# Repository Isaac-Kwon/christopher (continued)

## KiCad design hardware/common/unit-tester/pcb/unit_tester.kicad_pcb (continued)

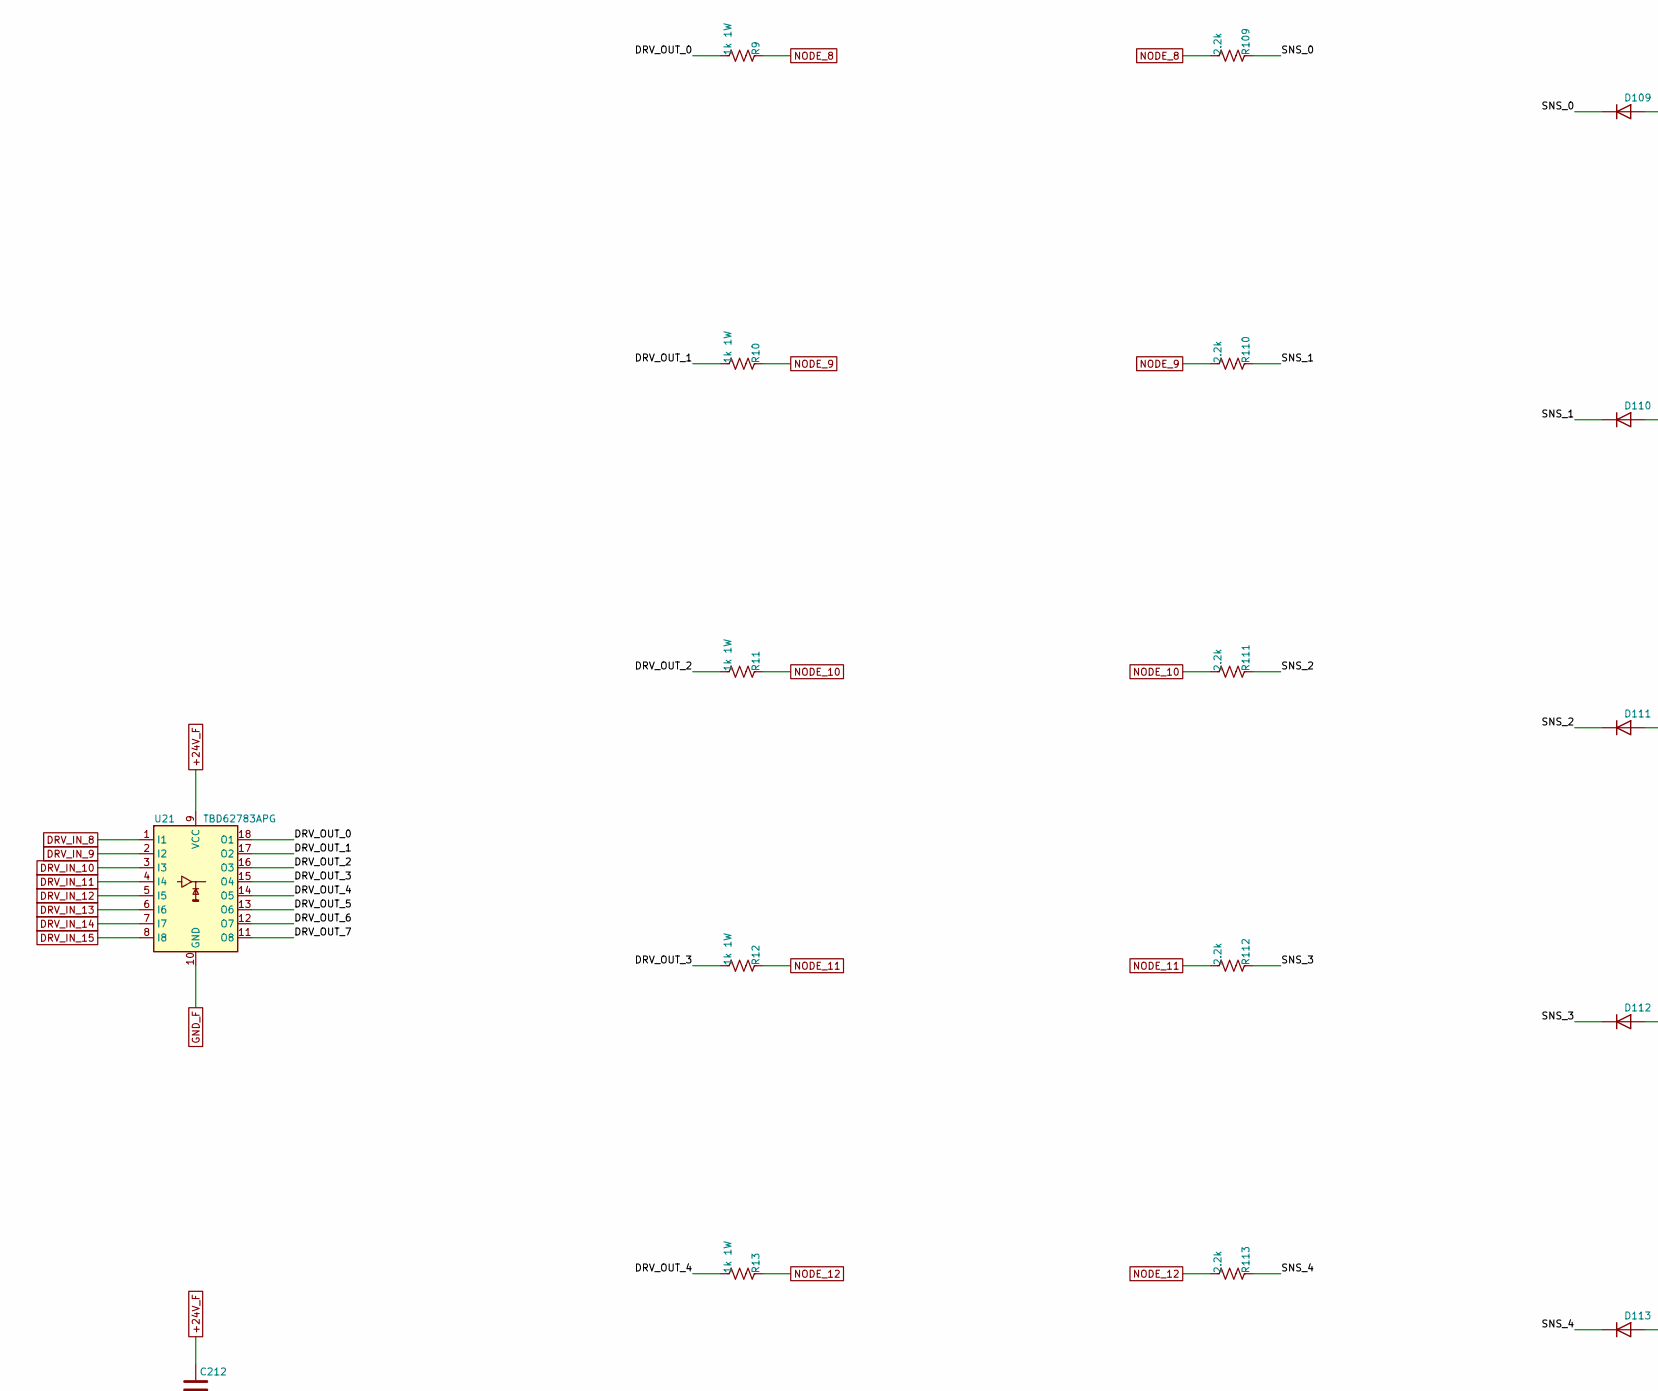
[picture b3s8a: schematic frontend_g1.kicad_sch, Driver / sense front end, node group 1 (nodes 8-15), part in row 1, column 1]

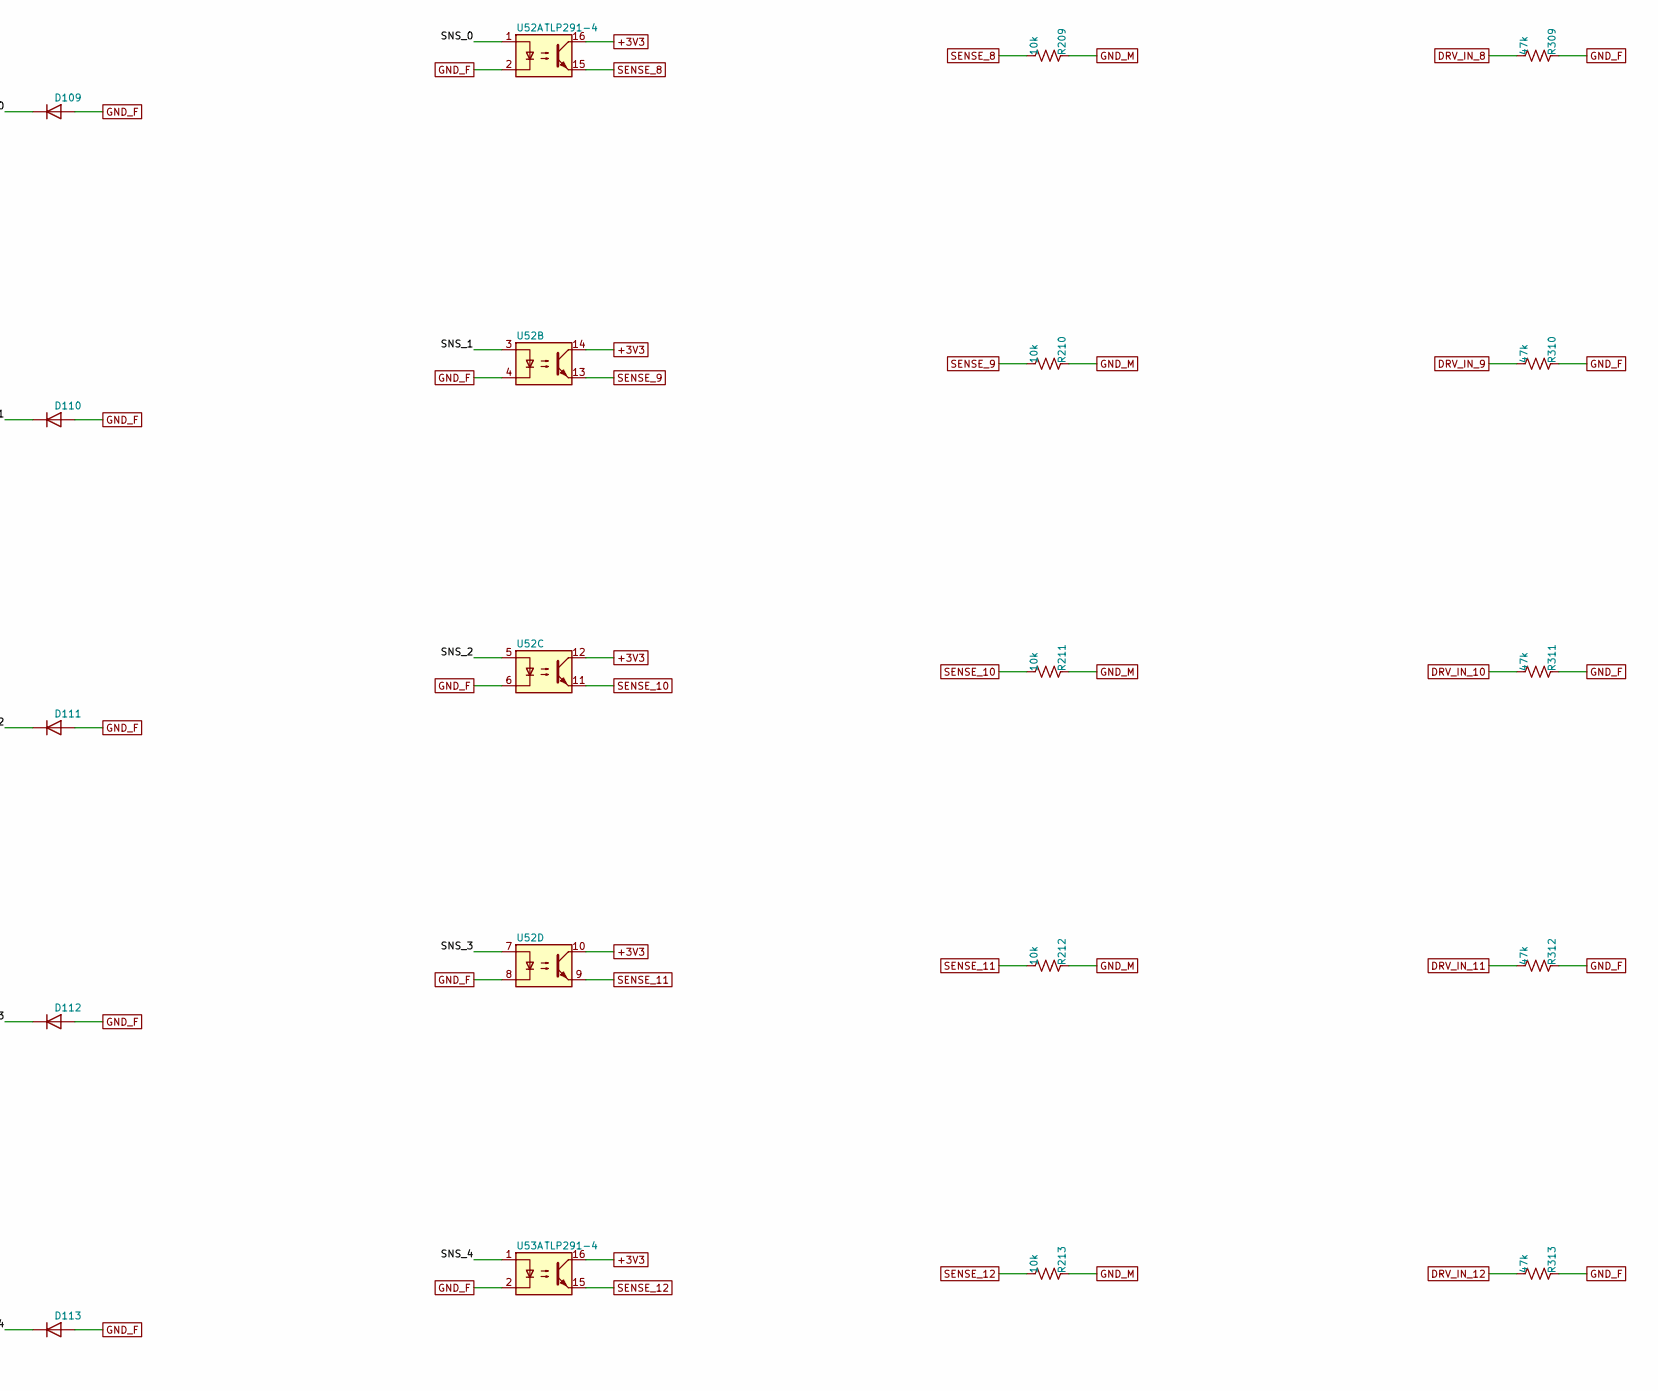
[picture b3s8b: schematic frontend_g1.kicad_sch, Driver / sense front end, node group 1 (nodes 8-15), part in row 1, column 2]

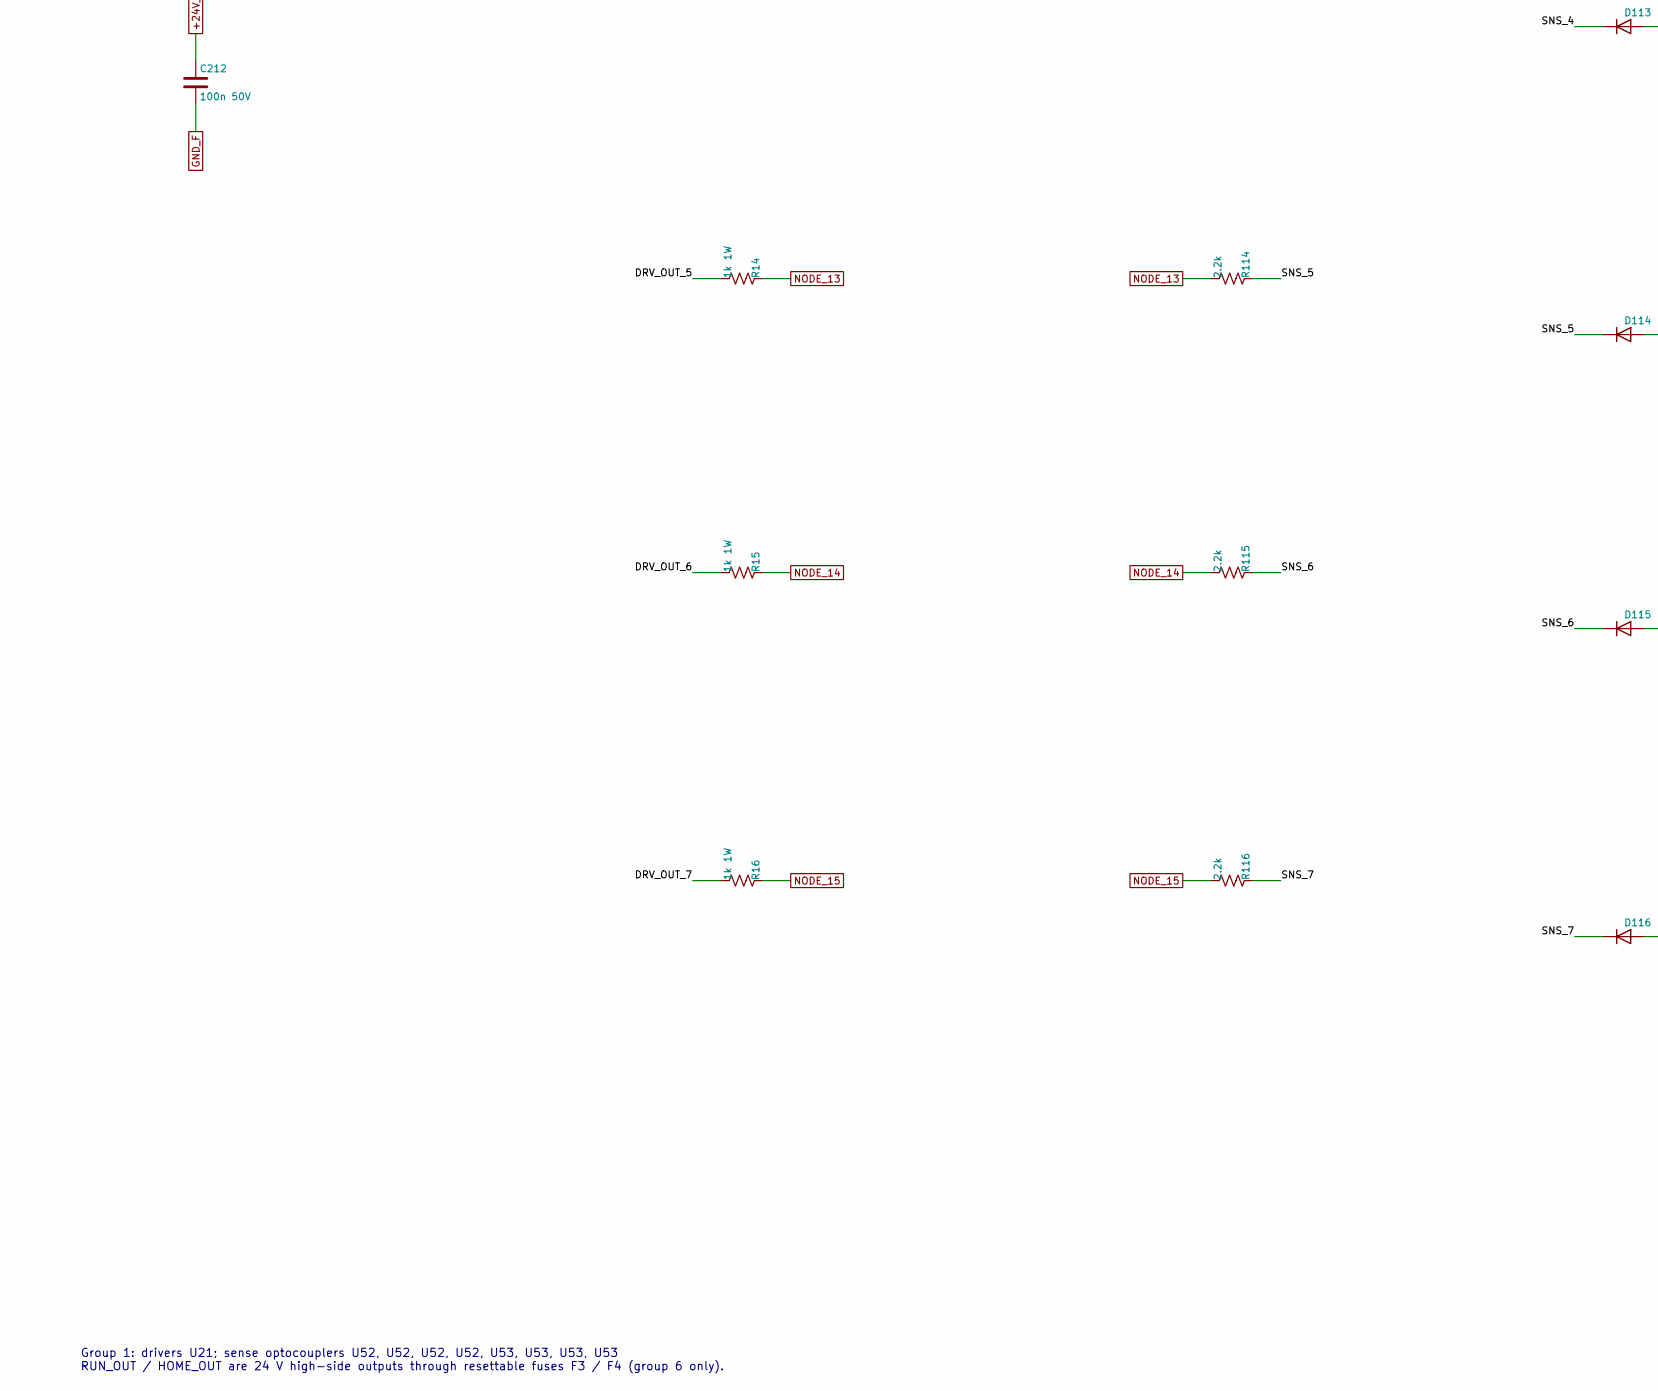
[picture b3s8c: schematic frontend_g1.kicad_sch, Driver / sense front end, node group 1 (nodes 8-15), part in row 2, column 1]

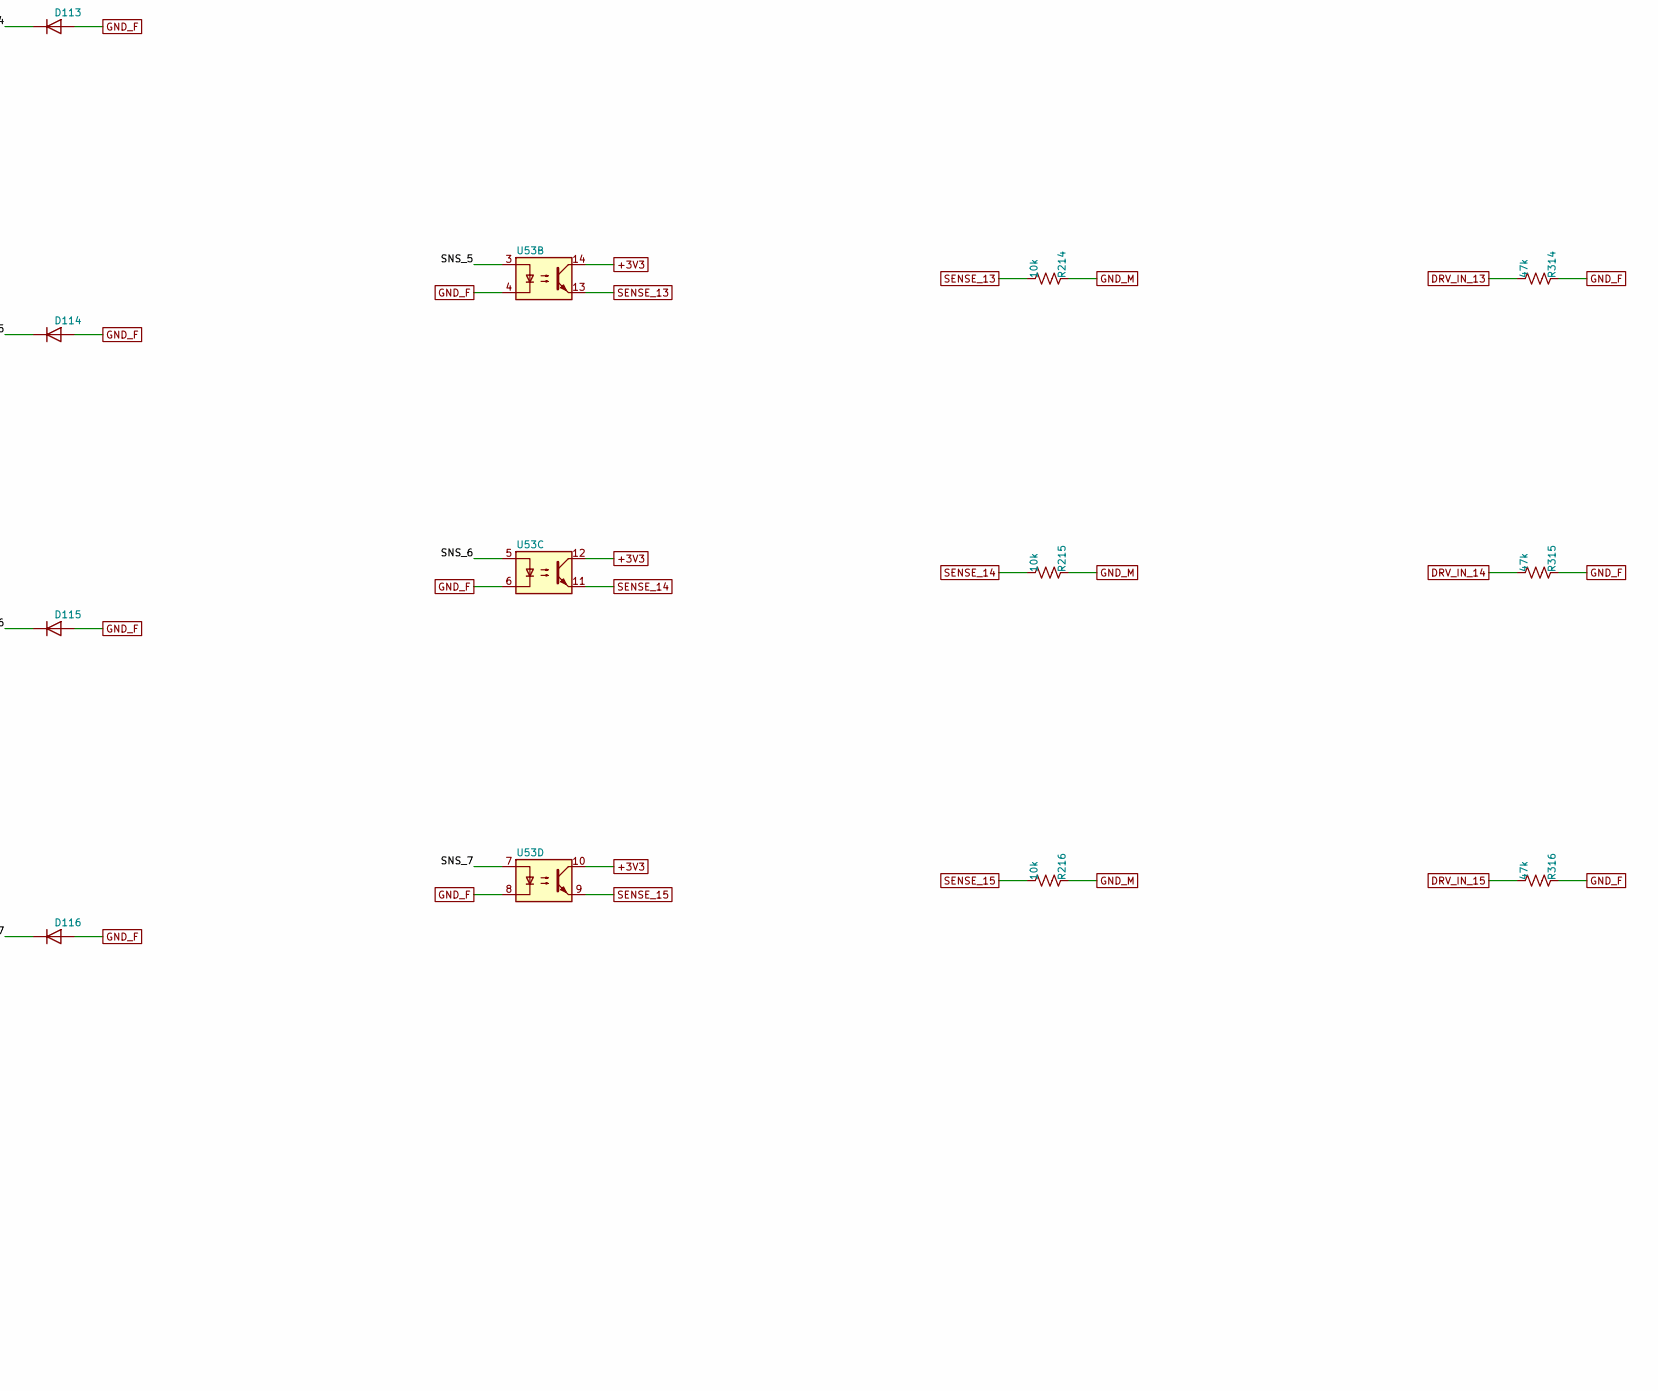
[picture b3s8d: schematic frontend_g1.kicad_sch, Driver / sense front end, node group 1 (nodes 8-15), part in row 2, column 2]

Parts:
C212: 100n 50V; C_0805_2012Metric
D109, D110, D111, D112, D113, D114, D115, D116: 1N4148W; D_SOD-123
R9, R10, R11, R12, R13, R14, R15, R16: 1k 1W; R_2512_6332Metric
R109, R110, R111, R112, R113, R114, R115, R116: 2.2k; R_0603_1608Metric
R209, R210, R211, R212, R213, R214, R215, R216: 10k; R_0603_1608Metric
R309, R310, R311, R312, R313, R314, R315, R316: 47k; R_0603_1608Metric
U21: TBD62783APG; SOIC-18W_7.5x11.6mm_P1.27mm
U52, U53: TLP291-4; SOIC-16_4.55x10.3mm_P1.27mm

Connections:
+3V3: U52.10, U52.12, U52.14, U52.16, U53.10, U53.12, U53.14, U53.16; also elsewhere on the board
+24V_F: C212.1, U21.9 (VCC); also elsewhere on the board
/FRONTEND_G1/DRV_OUT_0: R9.1, U21.18 (O1)
/FRONTEND_G1/DRV_OUT_1: R10.1, U21.17 (O2)
/FRONTEND_G1/DRV_OUT_2: R11.1, U21.16 (O3)
/FRONTEND_G1/DRV_OUT_3: R12.1, U21.15 (O4)
/FRONTEND_G1/DRV_OUT_4: R13.1, U21.14 (O5)
/FRONTEND_G1/DRV_OUT_5: R14.1, U21.13 (O6)
/FRONTEND_G1/DRV_OUT_6: R15.1, U21.12 (O7)
/FRONTEND_G1/DRV_OUT_7: R16.1, U21.11 (O8)
/FRONTEND_G1/SNS_0: D109.1 (K), R109.2, U52.1
/FRONTEND_G1/SNS_1: D110.1 (K), R110.2, U52.3
/FRONTEND_G1/SNS_2: D111.1 (K), R111.2, U52.5
/FRONTEND_G1/SNS_3: D112.1 (K), R112.2, U52.7
/FRONTEND_G1/SNS_4: D113.1 (K), R113.2, U53.1
/FRONTEND_G1/SNS_5: D114.1 (K), R114.2, U53.3
/FRONTEND_G1/SNS_6: D115.1 (K), R115.2, U53.5
/FRONTEND_G1/SNS_7: D116.1 (K), R116.2, U53.7
DRV_IN_8: R309.1, U21.1 (I1); also elsewhere on the board
DRV_IN_9: R310.1, U21.2 (I2); also elsewhere on the board
DRV_IN_10: R311.1, U21.3 (I3); also elsewhere on the board
DRV_IN_11: R312.1, U21.4 (I4); also elsewhere on the board
DRV_IN_12: R313.1, U21.5 (I5); also elsewhere on the board
DRV_IN_13: R314.1, U21.6 (I6); also elsewhere on the board
DRV_IN_14: R315.1, U21.7 (I7); also elsewhere on the board
DRV_IN_15: R316.1, U21.8 (I8); also elsewhere on the board
GND_F: C212.2, D109.2 (A), D110.2 (A), D111.2 (A), D112.2 (A), D113.2 (A), D114.2 (A), D115.2 (A), D116.2 (A), R309.2, R310.2, R311.2, R312.2, R313.2, R314.2, R315.2, R316.2, U21.10 (GND), U52.2, U52.4, U52.6, U52.8, U53.2, U53.4, U53.6, U53.8; also elsewhere on the board
GND_M: R209.2, R210.2, R211.2, R212.2, R213.2, R214.2, R215.2, R216.2; also elsewhere on the board
NODE_8: R9.2, R109.1; also elsewhere on the board
NODE_9: R10.2, R110.1; also elsewhere on the board
NODE_10: R11.2, R111.1; also elsewhere on the board
NODE_11: R12.2, R112.1; also elsewhere on the board
NODE_12: R13.2, R113.1; also elsewhere on the board
NODE_13: R14.2, R114.1; also elsewhere on the board
NODE_14: R15.2, R115.1; also elsewhere on the board
NODE_15: R16.2, R116.1; also elsewhere on the board
SENSE_8: R209.1, U52.15; also elsewhere on the board
SENSE_9: R210.1, U52.13; also elsewhere on the board
SENSE_10: R211.1, U52.11; also elsewhere on the board
SENSE_11: R212.1, U52.9; also elsewhere on the board
SENSE_12: R213.1, U53.15; also elsewhere on the board
SENSE_13: R214.1, U53.13; also elsewhere on the board
SENSE_14: R215.1, U53.11; also elsewhere on the board
SENSE_15: R216.1, U53.9; also elsewhere on the board

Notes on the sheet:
Group 1: drivers U21; sense optocouplers U52, U52, U52, U52, U53, U53, U53, U53 RUN_OUT / HOME_OUT are 24 V high-side outputs through resettable fuses F3 / F4 (group 6 only).

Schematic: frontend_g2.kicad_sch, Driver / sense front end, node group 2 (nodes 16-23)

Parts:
C213: 100n 50V; C_0805_2012Metric
D117, D118, D119, D120, D121, D122, D123, D124: 1N4148W; D_SOD-123
R17, R18, R19, R20, R21, R22, R23, R24: 1k 1W; R_2512_6332Metric
R117, R118, R119, R120, R121, R122, R123, R124: 2.2k; R_0603_1608Metric
R217, R218, R219, R220, R221, R222, R223, R224: 10k; R_0603_1608Metric
R317, R318, R319, R320, R321, R322, R323, R324: 47k; R_0603_1608Metric
U22: TBD62783APG; SOIC-18W_7.5x11.6mm_P1.27mm
U54, U55: TLP291-4; SOIC-16_4.55x10.3mm_P1.27mm

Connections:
+3V3: U54.10, U54.12, U54.14, U54.16, U55.10, U55.12, U55.14, U55.16; also elsewhere on the board
+24V_F: C213.1, U22.9 (VCC); also elsewhere on the board
/FRONTEND_G2/DRV_OUT_0: R17.1, U22.18 (O1)
/FRONTEND_G2/DRV_OUT_1: R18.1, U22.17 (O2)
/FRONTEND_G2/DRV_OUT_2: R19.1, U22.16 (O3)
/FRONTEND_G2/DRV_OUT_3: R20.1, U22.15 (O4)
/FRONTEND_G2/DRV_OUT_4: R21.1, U22.14 (O5)
/FRONTEND_G2/DRV_OUT_5: R22.1, U22.13 (O6)
/FRONTEND_G2/DRV_OUT_6: R23.1, U22.12 (O7)
/FRONTEND_G2/DRV_OUT_7: R24.1, U22.11 (O8)
/FRONTEND_G2/SNS_0: D117.1 (K), R117.2, U54.1
/FRONTEND_G2/SNS_1: D118.1 (K), R118.2, U54.3
/FRONTEND_G2/SNS_2: D119.1 (K), R119.2, U54.5
/FRONTEND_G2/SNS_3: D120.1 (K), R120.2, U54.7
/FRONTEND_G2/SNS_4: D121.1 (K), R121.2, U55.1
/FRONTEND_G2/SNS_5: D122.1 (K), R122.2, U55.3
/FRONTEND_G2/SNS_6: D123.1 (K), R123.2, U55.5
/FRONTEND_G2/SNS_7: D124.1 (K), R124.2, U55.7
DRV_IN_16: R317.1, U22.1 (I1); also elsewhere on the board
DRV_IN_17: R318.1, U22.2 (I2); also elsewhere on the board
DRV_IN_18: R319.1, U22.3 (I3); also elsewhere on the board
DRV_IN_19: R320.1, U22.4 (I4); also elsewhere on the board
DRV_IN_20: R321.1, U22.5 (I5); also elsewhere on the board
DRV_IN_21: R322.1, U22.6 (I6); also elsewhere on the board
DRV_IN_22: R323.1, U22.7 (I7); also elsewhere on the board
DRV_IN_23: R324.1, U22.8 (I8); also elsewhere on the board
GND_F: C213.2, D117.2 (A), D118.2 (A), D119.2 (A), D120.2 (A), D121.2 (A), D122.2 (A), D123.2 (A), D124.2 (A), R317.2, R318.2, R319.2, R320.2, R321.2, R322.2, R323.2, R324.2, U22.10 (GND), U54.2, U54.4, U54.6, U54.8, U55.2, U55.4, U55.6, U55.8; also elsewhere on the board
GND_M: R217.2, R218.2, R219.2, R220.2, R221.2, R222.2, R223.2, R224.2; also elsewhere on the board
NODE_16: R17.2, R117.1; also elsewhere on the board
NODE_17: R18.2, R118.1; also elsewhere on the board
NODE_18: R19.2, R119.1; also elsewhere on the board
NODE_19: R20.2, R120.1; also elsewhere on the board
NODE_20: R21.2, R121.1; also elsewhere on the board
NODE_21: R22.2, R122.1; also elsewhere on the board
NODE_22: R23.2, R123.1; also elsewhere on the board
NODE_23: R24.2, R124.1; also elsewhere on the board
SENSE_16: R217.1, U54.15; also elsewhere on the board
SENSE_17: R218.1, U54.13; also elsewhere on the board
SENSE_18: R219.1, U54.11; also elsewhere on the board
SENSE_19: R220.1, U54.9; also elsewhere on the board
SENSE_20: R221.1, U55.15; also elsewhere on the board
SENSE_21: R222.1, U55.13; also elsewhere on the board
SENSE_22: R223.1, U55.11; also elsewhere on the board
SENSE_23: R224.1, U55.9; also elsewhere on the board

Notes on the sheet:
Group 2: drivers U22; sense optocouplers U54, U54, U54, U54, U55, U55, U55, U55 RUN_OUT / HOME_OUT are 24 V high-side outputs through resettable fuses F3 / F4 (group 6 only).

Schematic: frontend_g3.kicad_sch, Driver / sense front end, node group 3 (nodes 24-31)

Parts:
C214: 100n 50V; C_0805_2012Metric
D125, D126, D127, D128, D129, D130, D131, D132: 1N4148W; D_SOD-123
R25, R26, R27, R28, R29, R30, R31, R32: 1k 1W; R_2512_6332Metric
R125, R126, R127, R128, R129, R130, R131, R132: 2.2k; R_0603_1608Metric
R225, R226, R227, R228, R229, R230, R231, R232: 10k; R_0603_1608Metric
R325, R326, R327, R328, R329, R330, R331, R332: 47k; R_0603_1608Metric
U23: TBD62783APG; SOIC-18W_7.5x11.6mm_P1.27mm
U56, U57: TLP291-4; SOIC-16_4.55x10.3mm_P1.27mm

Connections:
+3V3: U56.10, U56.12, U56.14, U56.16, U57.10, U57.12, U57.14, U57.16; also elsewhere on the board
+24V_F: C214.1, U23.9 (VCC); also elsewhere on the board
/FRONTEND_G3/DRV_OUT_0: R25.1, U23.18 (O1)
/FRONTEND_G3/DRV_OUT_1: R26.1, U23.17 (O2)
/FRONTEND_G3/DRV_OUT_2: R27.1, U23.16 (O3)
/FRONTEND_G3/DRV_OUT_3: R28.1, U23.15 (O4)
/FRONTEND_G3/DRV_OUT_4: R29.1, U23.14 (O5)
/FRONTEND_G3/DRV_OUT_5: R30.1, U23.13 (O6)
/FRONTEND_G3/DRV_OUT_6: R31.1, U23.12 (O7)
/FRONTEND_G3/DRV_OUT_7: R32.1, U23.11 (O8)
/FRONTEND_G3/SNS_0: D125.1 (K), R125.2, U56.1
/FRONTEND_G3/SNS_1: D126.1 (K), R126.2, U56.3
/FRONTEND_G3/SNS_2: D127.1 (K), R127.2, U56.5
/FRONTEND_G3/SNS_3: D128.1 (K), R128.2, U56.7
/FRONTEND_G3/SNS_4: D129.1 (K), R129.2, U57.1
/FRONTEND_G3/SNS_5: D130.1 (K), R130.2, U57.3
/FRONTEND_G3/SNS_6: D131.1 (K), R131.2, U57.5
/FRONTEND_G3/SNS_7: D132.1 (K), R132.2, U57.7
DRV_IN_24: R325.1, U23.1 (I1); also elsewhere on the board
DRV_IN_25: R326.1, U23.2 (I2); also elsewhere on the board
DRV_IN_26: R327.1, U23.3 (I3); also elsewhere on the board
DRV_IN_27: R328.1, U23.4 (I4); also elsewhere on the board
DRV_IN_28: R329.1, U23.5 (I5); also elsewhere on the board
DRV_IN_29: R330.1, U23.6 (I6); also elsewhere on the board
DRV_IN_30: R331.1, U23.7 (I7); also elsewhere on the board
DRV_IN_31: R332.1, U23.8 (I8); also elsewhere on the board
GND_F: C214.2, D125.2 (A), D126.2 (A), D127.2 (A), D128.2 (A), D129.2 (A), D130.2 (A), D131.2 (A), D132.2 (A), R325.2, R326.2, R327.2, R328.2, R329.2, R330.2, R331.2, R332.2, U23.10 (GND), U56.2, U56.4, U56.6, U56.8, U57.2, U57.4, U57.6, U57.8; also elsewhere on the board
GND_M: R225.2, R226.2, R227.2, R228.2, R229.2, R230.2, R231.2, R232.2; also elsewhere on the board
NODE_24: R25.2, R125.1; also elsewhere on the board
NODE_25: R26.2, R126.1; also elsewhere on the board
NODE_26: R27.2, R127.1; also elsewhere on the board
NODE_27: R28.2, R128.1; also elsewhere on the board
NODE_28: R29.2, R129.1; also elsewhere on the board
NODE_29: R30.2, R130.1; also elsewhere on the board
NODE_30: R31.2, R131.1; also elsewhere on the board
NODE_31: R32.2, R132.1; also elsewhere on the board
SENSE_24: R225.1, U56.15; also elsewhere on the board
SENSE_25: R226.1, U56.13; also elsewhere on the board
SENSE_26: R227.1, U56.11; also elsewhere on the board
SENSE_27: R228.1, U56.9; also elsewhere on the board
SENSE_28: R229.1, U57.15; also elsewhere on the board
SENSE_29: R230.1, U57.13; also elsewhere on the board
SENSE_30: R231.1, U57.11; also elsewhere on the board
SENSE_31: R232.1, U57.9; also elsewhere on the board

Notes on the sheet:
Group 3: drivers U23; sense optocouplers U56, U56, U56, U56, U57, U57, U57, U57 RUN_OUT / HOME_OUT are 24 V high-side outputs through resettable fuses F3 / F4 (group 6 only).

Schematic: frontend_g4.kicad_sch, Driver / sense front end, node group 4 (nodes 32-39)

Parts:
C215: 100n 50V; C_0805_2012Metric
D133, D134, D135, D136, D137, D138, D139, D140: 1N4148W; D_SOD-123
R33, R34, R35, R36, R37, R38, R39, R40: 1k 1W; R_2512_6332Metric
R133, R134, R135, R136, R137, R138, R139, R140: 2.2k; R_0603_1608Metric
R233, R234, R235, R236, R237, R238, R239, R240: 10k; R_0603_1608Metric
R333, R334, R335, R336, R337, R338, R339, R340: 47k; R_0603_1608Metric
U24: TBD62783APG; SOIC-18W_7.5x11.6mm_P1.27mm
U58, U59: TLP291-4; SOIC-16_4.55x10.3mm_P1.27mm

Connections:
+3V3: U58.10, U58.12, U58.14, U58.16, U59.10, U59.12, U59.14, U59.16; also elsewhere on the board
+24V_F: C215.1, U24.9 (VCC); also elsewhere on the board
/FRONTEND_G4/DRV_OUT_0: R33.1, U24.18 (O1)
/FRONTEND_G4/DRV_OUT_1: R34.1, U24.17 (O2)
/FRONTEND_G4/DRV_OUT_2: R35.1, U24.16 (O3)
/FRONTEND_G4/DRV_OUT_3: R36.1, U24.15 (O4)
/FRONTEND_G4/DRV_OUT_4: R37.1, U24.14 (O5)
/FRONTEND_G4/DRV_OUT_5: R38.1, U24.13 (O6)
/FRONTEND_G4/DRV_OUT_6: R39.1, U24.12 (O7)
/FRONTEND_G4/DRV_OUT_7: R40.1, U24.11 (O8)
/FRONTEND_G4/SNS_0: D133.1 (K), R133.2, U58.1
/FRONTEND_G4/SNS_1: D134.1 (K), R134.2, U58.3
/FRONTEND_G4/SNS_2: D135.1 (K), R135.2, U58.5
/FRONTEND_G4/SNS_3: D136.1 (K), R136.2, U58.7
/FRONTEND_G4/SNS_4: D137.1 (K), R137.2, U59.1
/FRONTEND_G4/SNS_5: D138.1 (K), R138.2, U59.3
/FRONTEND_G4/SNS_6: D139.1 (K), R139.2, U59.5
/FRONTEND_G4/SNS_7: D140.1 (K), R140.2, U59.7
DRV_IN_32: R333.1, U24.1 (I1); also elsewhere on the board
DRV_IN_33: R334.1, U24.2 (I2); also elsewhere on the board
DRV_IN_34: R335.1, U24.3 (I3); also elsewhere on the board
DRV_IN_35: R336.1, U24.4 (I4); also elsewhere on the board
DRV_IN_36: R337.1, U24.5 (I5); also elsewhere on the board
DRV_IN_37: R338.1, U24.6 (I6); also elsewhere on the board
DRV_IN_38: R339.1, U24.7 (I7); also elsewhere on the board
DRV_IN_39: R340.1, U24.8 (I8); also elsewhere on the board
GND_F: C215.2, D133.2 (A), D134.2 (A), D135.2 (A), D136.2 (A), D137.2 (A), D138.2 (A), D139.2 (A), D140.2 (A), R333.2, R334.2, R335.2, R336.2, R337.2, R338.2, R339.2, R340.2, U24.10 (GND), U58.2, U58.4, U58.6, U58.8, U59.2, U59.4, U59.6, U59.8; also elsewhere on the board
GND_M: R233.2, R234.2, R235.2, R236.2, R237.2, R238.2, R239.2, R240.2; also elsewhere on the board
NODE_32: R33.2, R133.1; also elsewhere on the board
NODE_33: R34.2, R134.1; also elsewhere on the board
NODE_34: R35.2, R135.1; also elsewhere on the board
NODE_35: R36.2, R136.1; also elsewhere on the board
NODE_36: R37.2, R137.1; also elsewhere on the board
NODE_37: R38.2, R138.1; also elsewhere on the board
NODE_38: R39.2, R139.1; also elsewhere on the board
NODE_39: R40.2, R140.1; also elsewhere on the board
SENSE_32: R233.1, U58.15; also elsewhere on the board
SENSE_33: R234.1, U58.13; also elsewhere on the board
SENSE_34: R235.1, U58.11; also elsewhere on the board
SENSE_35: R236.1, U58.9; also elsewhere on the board
SENSE_36: R237.1, U59.15; also elsewhere on the board
SENSE_37: R238.1, U59.13; also elsewhere on the board
SENSE_38: R239.1, U59.11; also elsewhere on the board
SENSE_39: R240.1, U59.9; also elsewhere on the board

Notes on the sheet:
Group 4: drivers U24; sense optocouplers U58, U58, U58, U58, U59, U59, U59, U59 RUN_OUT / HOME_OUT are 24 V high-side outputs through resettable fuses F3 / F4 (group 6 only).

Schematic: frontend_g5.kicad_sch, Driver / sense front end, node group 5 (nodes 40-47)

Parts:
C216: 100n 50V; C_0805_2012Metric
D141, D142, D143, D144, D145, D146, D147, D148: 1N4148W; D_SOD-123
R41, R42, R43, R44, R45, R46, R47, R48: 1k 1W; R_2512_6332Metric
R141, R142, R143, R144, R145, R146, R147, R148: 2.2k; R_0603_1608Metric
R241, R242, R243, R244, R245, R246, R247, R248: 10k; R_0603_1608Metric
R341, R342, R343, R344, R345, R346, R347, R348: 47k; R_0603_1608Metric
U25: TBD62783APG; SOIC-18W_7.5x11.6mm_P1.27mm
U60, U61: TLP291-4; SOIC-16_4.55x10.3mm_P1.27mm

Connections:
+3V3: U60.10, U60.12, U60.14, U60.16, U61.10, U61.12, U61.14, U61.16; also elsewhere on the board
+24V_F: C216.1, U25.9 (VCC); also elsewhere on the board
/FRONTEND_G5/DRV_OUT_0: R41.1, U25.18 (O1)
/FRONTEND_G5/DRV_OUT_1: R42.1, U25.17 (O2)
/FRONTEND_G5/DRV_OUT_2: R43.1, U25.16 (O3)
/FRONTEND_G5/DRV_OUT_3: R44.1, U25.15 (O4)
/FRONTEND_G5/DRV_OUT_4: R45.1, U25.14 (O5)
/FRONTEND_G5/DRV_OUT_5: R46.1, U25.13 (O6)
/FRONTEND_G5/DRV_OUT_6: R47.1, U25.12 (O7)
/FRONTEND_G5/DRV_OUT_7: R48.1, U25.11 (O8)
/FRONTEND_G5/SNS_0: D141.1 (K), R141.2, U60.1
/FRONTEND_G5/SNS_1: D142.1 (K), R142.2, U60.3
/FRONTEND_G5/SNS_2: D143.1 (K), R143.2, U60.5
/FRONTEND_G5/SNS_3: D144.1 (K), R144.2, U60.7
/FRONTEND_G5/SNS_4: D145.1 (K), R145.2, U61.1
/FRONTEND_G5/SNS_5: D146.1 (K), R146.2, U61.3
/FRONTEND_G5/SNS_6: D147.1 (K), R147.2, U61.5
/FRONTEND_G5/SNS_7: D148.1 (K), R148.2, U61.7
DRV_IN_40: R341.1, U25.1 (I1); also elsewhere on the board
DRV_IN_41: R342.1, U25.2 (I2); also elsewhere on the board
DRV_IN_42: R343.1, U25.3 (I3); also elsewhere on the board
DRV_IN_43: R344.1, U25.4 (I4); also elsewhere on the board
DRV_IN_44: R345.1, U25.5 (I5); also elsewhere on the board
DRV_IN_45: R346.1, U25.6 (I6); also elsewhere on the board
DRV_IN_46: R347.1, U25.7 (I7); also elsewhere on the board
DRV_IN_47: R348.1, U25.8 (I8); also elsewhere on the board
GND_F: C216.2, D141.2 (A), D142.2 (A), D143.2 (A), D144.2 (A), D145.2 (A), D146.2 (A), D147.2 (A), D148.2 (A), R341.2, R342.2, R343.2, R344.2, R345.2, R346.2, R347.2, R348.2, U25.10 (GND), U60.2, U60.4, U60.6, U60.8, U61.2, U61.4, U61.6, U61.8; also elsewhere on the board
GND_M: R241.2, R242.2, R243.2, R244.2, R245.2, R246.2, R247.2, R248.2; also elsewhere on the board
NODE_40: R41.2, R141.1; also elsewhere on the board
NODE_41: R42.2, R142.1; also elsewhere on the board
NODE_42: R43.2, R143.1; also elsewhere on the board
NODE_43: R44.2, R144.1; also elsewhere on the board
NODE_44: R45.2, R145.1; also elsewhere on the board
NODE_45: R46.2, R146.1; also elsewhere on the board
NODE_46: R47.2, R147.1; also elsewhere on the board
NODE_47: R48.2, R148.1; also elsewhere on the board
SENSE_40: R241.1, U60.15; also elsewhere on the board
SENSE_41: R242.1, U60.13; also elsewhere on the board
SENSE_42: R243.1, U60.11; also elsewhere on the board
SENSE_43: R244.1, U60.9; also elsewhere on the board
SENSE_44: R245.1, U61.15; also elsewhere on the board
SENSE_45: R246.1, U61.13; also elsewhere on the board
SENSE_46: R247.1, U61.11; also elsewhere on the board
SENSE_47: R248.1, U61.9; also elsewhere on the board

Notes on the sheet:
Group 5: drivers U25; sense optocouplers U60, U60, U60, U60, U61, U61, U61, U61 RUN_OUT / HOME_OUT are 24 V high-side outputs through resettable fuses F3 / F4 (group 6 only).

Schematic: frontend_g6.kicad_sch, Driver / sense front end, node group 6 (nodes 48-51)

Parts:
C217: 100n 50V; C_0805_2012Metric
D149, D150, D151, D152: 1N4148W; D_SOD-123
F3, F4: PTC 30mA hold/100mA trip; Fuse_1206_3216Metric
R49, R50, R51, R52: 1k 1W; R_2512_6332Metric
R149, R150, R151, R152: 2.2k; R_0603_1608Metric
R249, R250, R251, R252: 10k; R_0603_1608Metric
R349, R350, R351, R352, R353, R354: 47k; R_0603_1608Metric
U26: TBD62783APG; SOIC-18W_7.5x11.6mm_P1.27mm
U62: TLP291-4; SOIC-16_4.55x10.3mm_P1.27mm

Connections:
+3V3: U62.10, U62.12, U62.14, U62.16; also elsewhere on the board
+24V_F: C217.1, U26.9 (VCC); also elsewhere on the board
/FRONTEND_G6/DRV_OUT_0: R49.1, U26.18 (O1)
/FRONTEND_G6/DRV_OUT_1: R50.1, U26.17 (O2)
/FRONTEND_G6/DRV_OUT_2: R51.1, U26.16 (O3)
/FRONTEND_G6/DRV_OUT_3: R52.1, U26.15 (O4)
/FRONTEND_G6/DRV_OUT_6: F3.1, U26.12 (O7)
/FRONTEND_G6/DRV_OUT_7: F4.1, U26.11 (O8)
/FRONTEND_G6/SNS_0: D149.1 (K), R149.2, U62.1
/FRONTEND_G6/SNS_1: D150.1 (K), R150.2, U62.3
/FRONTEND_G6/SNS_2: D151.1 (K), R151.2, U62.5
/FRONTEND_G6/SNS_3: D152.1 (K), R152.2, U62.7
DRV_IN_48: R349.1, U26.1 (I1); also elsewhere on the board
DRV_IN_49: R350.1, U26.2 (I2); also elsewhere on the board
DRV_IN_50: R351.1, U26.3 (I3); also elsewhere on the board
DRV_IN_51: R352.1, U26.4 (I4); also elsewhere on the board
DRV_IN_52: R353.1, U26.5 (I5); also elsewhere on the board
DRV_IN_53: R354.1, U26.6 (I6); also elsewhere on the board
GND_F: C217.2, D149.2 (A), D150.2 (A), D151.2 (A), D152.2 (A), R349.2, R350.2, R351.2, R352.2, R353.2, R354.2, U26.10 (GND), U62.2, U62.4, U62.6, U62.8; also elsewhere on the board
GND_M: R249.2, R250.2, R251.2, R252.2; also elsewhere on the board
HOME_F: U26.8 (I8); also elsewhere on the board
HOME_OUT: F4.2; also elsewhere on the board
NODE_48: R49.2, R149.1; also elsewhere on the board
NODE_49: R50.2, R150.1; also elsewhere on the board
NODE_50: R51.2, R151.1; also elsewhere on the board
NODE_51: R52.2, R152.1; also elsewhere on the board
RUN_F: U26.7 (I7); also elsewhere on the board
RUN_OUT: F3.2; also elsewhere on the board
SENSE_48: R249.1, U62.15; also elsewhere on the board
SENSE_49: R250.1, U62.13; also elsewhere on the board
SENSE_50: R251.1, U62.11; also elsewhere on the board
SENSE_51: R252.1, U62.9; also elsewhere on the board

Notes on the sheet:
Group 6: drivers U26; sense optocouplers U62, U62, U62, U62 RUN_OUT / HOME_OUT are 24 V high-side outputs through resettable fuses F3 / F4 (group 6 only).
